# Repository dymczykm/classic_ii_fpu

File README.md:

# Macintosh Classic II FPU card

This repo contains a KiCAD design of an expansion card that adds an MC68882 FPU to your Macintosh Classic II. The board has two layers to keep the PCB cost down. It offers a switchable clock source between the system clock (16 MHz, synchronous operation) and a crystal oscillator on the board (40 MHz, asynchronous operation; tested with MC68882FN40A, the rumours claim 50 MHz will work too).

### Results

After plugging in the card, it should be immediately visible in some tools (here System Information of MacBench):

The board dramatically improves the Floating Point performance of the computer. MacBench 1.0 with an FPU@16 MHz (system clock) reports over a 13x improvement.
When using an external 40 MHz oscillator, the Floating Point result goes up even a bit more - to 15.7x (it's not proportional to the clock frequency as at some point the slow 16-bit bus becomes a limiting factor):

(look at the Floating Point row)

### Order a PCB

If you want to order a PCB directly, I have created a project on PCBWay:
https://www.pcbway.com/project/shareproject/Macintosh_Classic_II_FPU_card.html

### Bill of Materials

| Qty | Value           | Device             | Package              | Parts                                                  | Digikey reference             | 
|-----|-----------------|--------------------|----------------------|--------------------------------------------------------|-------------------------------|
| 1   |                 | MC68882FN40A       | PLCC68               | IC1                                                    |                               | 
| 1   |                 | PLCC68 socket      | PLCC68               | hosts IC1                                              | 2057-PLCC-68-AT-ND            | 
| 1   |                 | TE 5-532955-8      |                      | J2                                                     | A34313-ND                     | 
| 1   |                 | Pin Header 2.54mm  | 3 pins               | J1                                                     |                               |
| 6   | 100nF X7R       | SMD capacitor      | 0805                 | C1-C5, C7                                              | 399-17169-6-ND                | 
| 1   | 10uF 10V        | Tantalum Cap       | A (3216)             | C6                                                     | 399-4788-1-ND                 | 
| 1   | 51 ohm          | SMD resistor       | 0805                 | R1                                                     | A126374CT-ND                  | 
| 1   | 40 MHz          | Crystal oscillator | DIP-8                | X1                                                     | e.g. MXO45HS-2C-40M000000     | 
| 1   |                 | Shunt jumper       |                      | over J1                                                | 881545-1                      | 

(sorry, I had most components at hand, so I only have Digikey references for the rather specific ones)

### Pictures

### References and Credits

The MC68000 KiCAD library from https://dev.sigpipe.me/DashieElectronics/Jackalope

Thanks to [pfuentes69](https://github.com/pfuentes69) for providing the missing Digikey PNs.

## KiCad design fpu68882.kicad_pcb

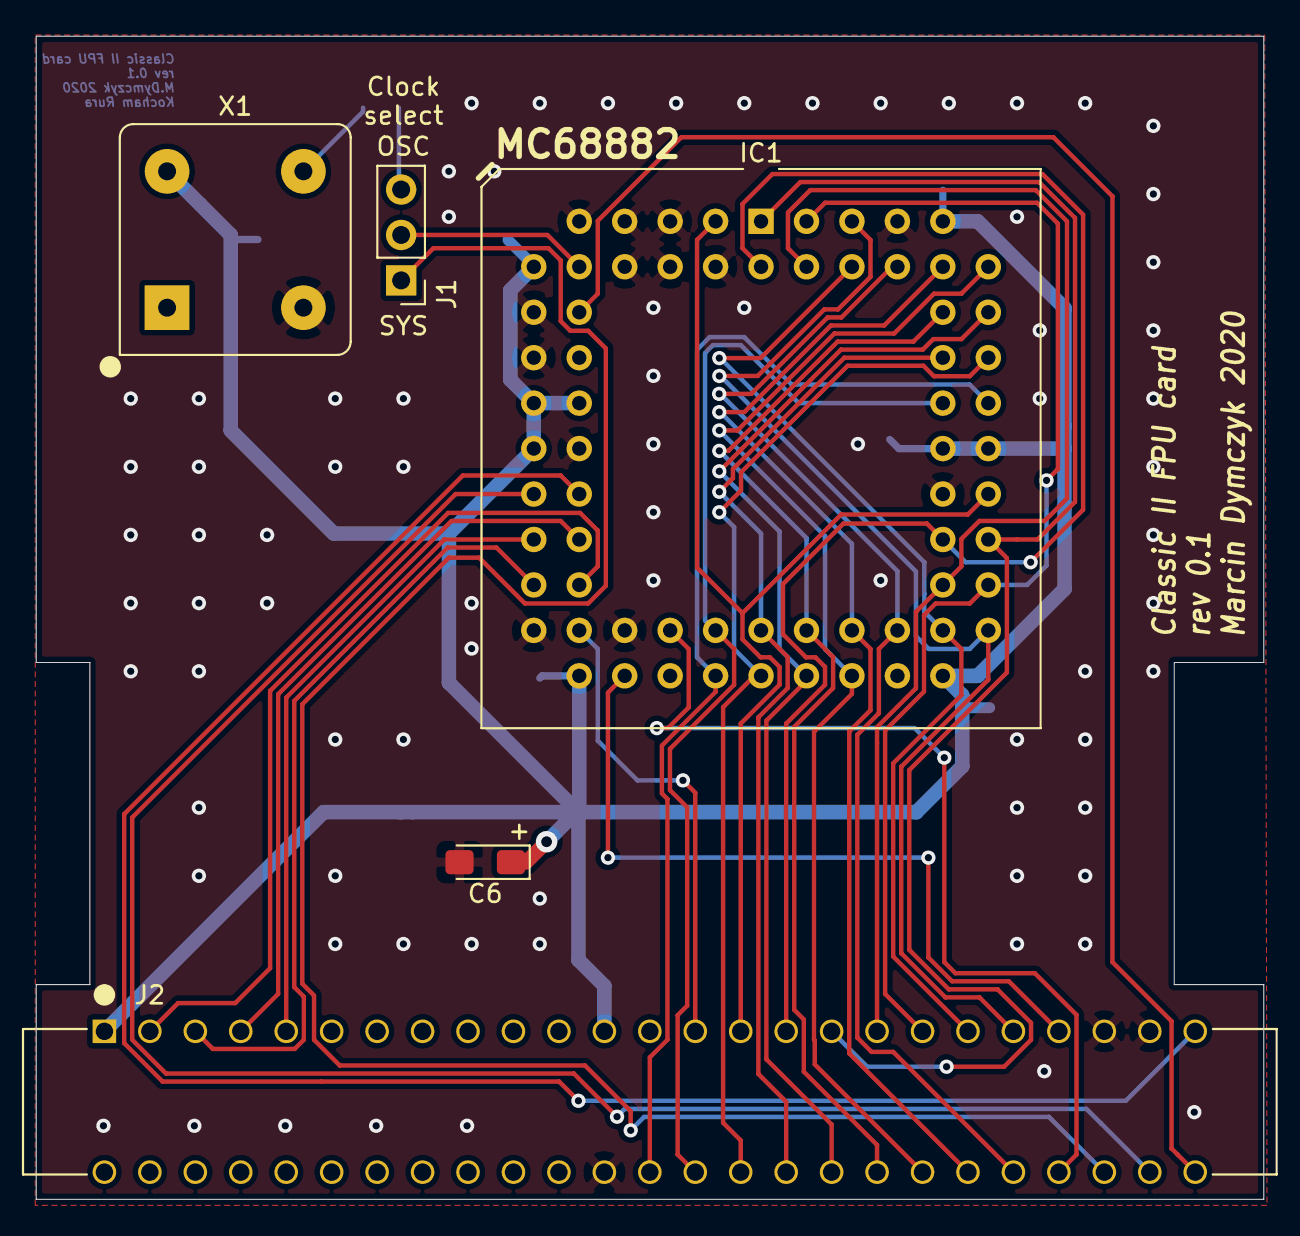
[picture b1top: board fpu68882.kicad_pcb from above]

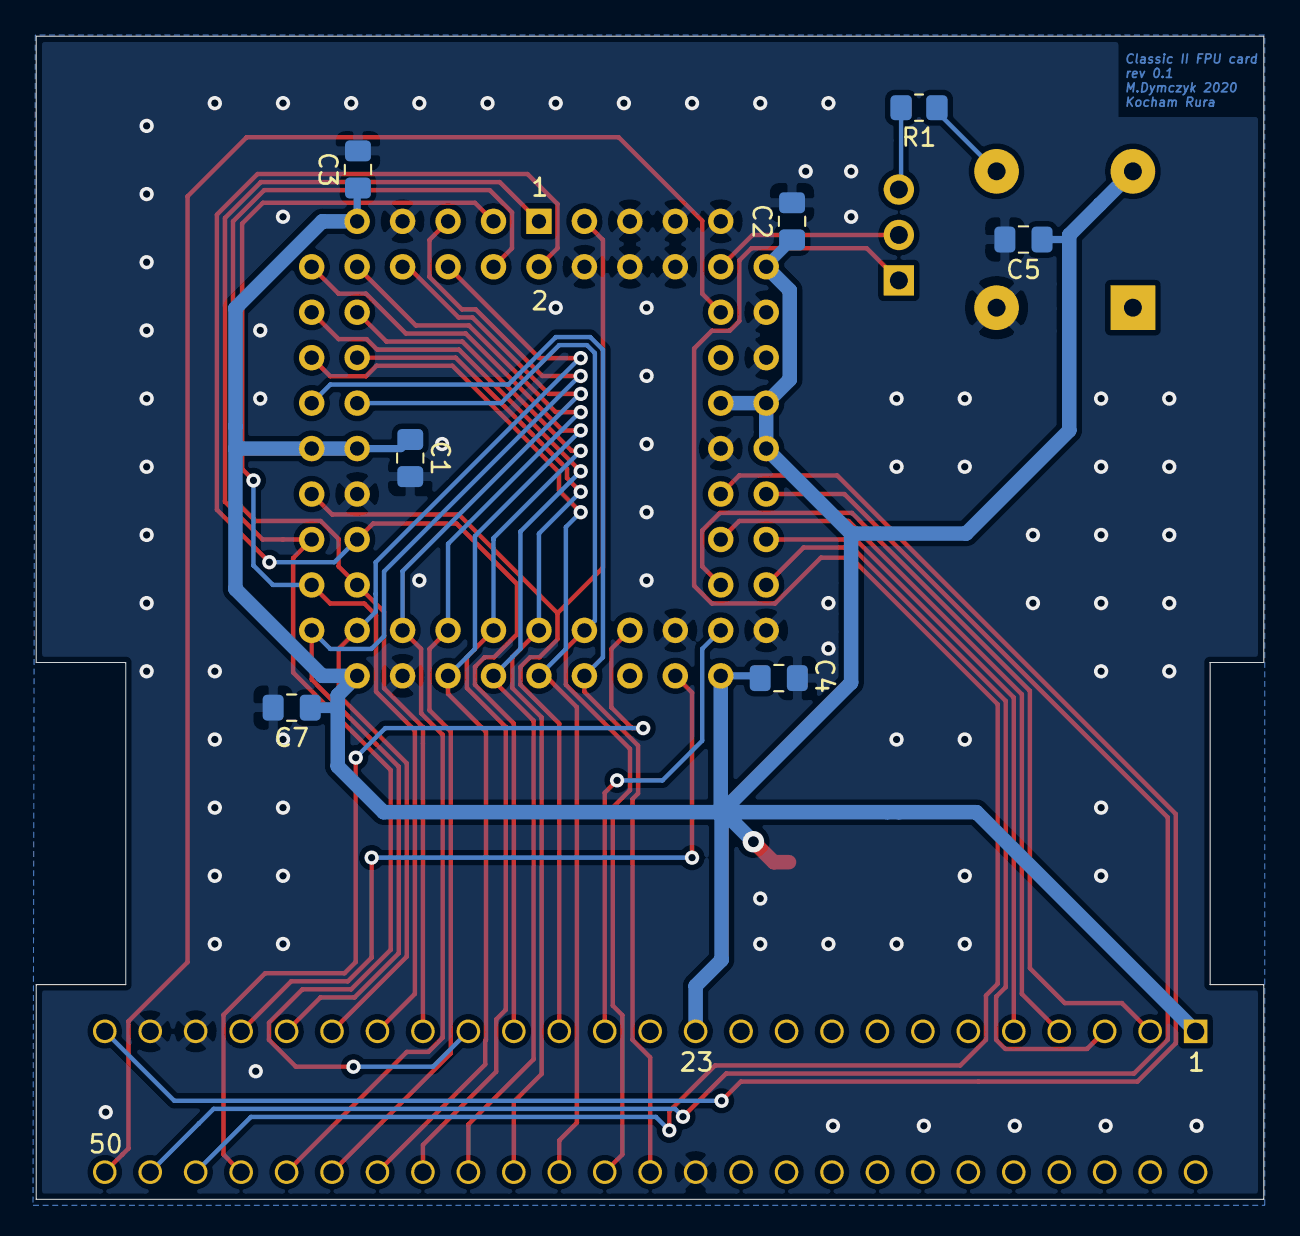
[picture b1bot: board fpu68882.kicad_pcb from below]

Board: 2 copper layers, 68.6 x 65.0 mm, 12 parts (7 on the bottom side), 32 nets.

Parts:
C1, C2, C3, C4, C5, C7: 100n; C_0805_2012Metric_Pad1.18x1.45mm_HandSolder
C6: 4u7; CP_EIA-3216-18_Kemet-A_Pad1.58x1.35mm_HandSolder
IC1: MC68881FN; PLCC-68_THT-Socket
J1: Conn_01x03; PinHeader_1x03_P2.54mm_Vertical
J2: Conn_02x25_Odd_Even; TE_5-532955-8_Odd_Even
R1: 33; R_0805_2012Metric_Pad1.20x1.40mm_HandSolder
X1: CXO_DIP8_40M; Oscillator_DIP-8_LargePads

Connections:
/A1: IC1.25, J2.3
/A2: IC1.24, J2.5
/A3: IC1.23, J2.7
/A4: IC1.22, J2.9
/C16M: J1.1, J2.46
/D16: IC1.3, IC1.50, J2.29
/D17: IC1.2, IC1.49, J2.31
/D18: IC1.1, IC1.48, J2.33
/D19: IC1.47, IC1.68, J2.35
/D20: IC1.46, IC1.67, J2.37
/D21: IC1.45, IC1.66, J2.39
/D22: IC1.44, IC1.65, J2.41
/D23: IC1.42, IC1.64, J2.42
/D24: IC1.40, IC1.62, J2.40
/D25: IC1.39, IC1.60, J2.38
/D26: IC1.38, IC1.59, J2.36
/D27: IC1.37, IC1.58, J2.34
/D28: IC1.36, IC1.57, J2.32
/D29: IC1.35, IC1.56, J2.30
/D30: IC1.34, IC1.55, J2.28
/D31: IC1.33, IC1.54, J2.26
/\AS: IC1.21, J2.49
/\DS: IC1.20, J2.48
/\DSACK1: IC1.32, J2.44
/\FPU.SEL: IC1.29, J2.43
/\RESET: IC1.13, J2.50
/\RW: IC1.28, J2.27
GND: C1.2, C2.2, C3.2, C4.2, C5.2, C6.2, C7.2, IC1.4, IC1.5, IC1.6, IC1.7, IC1.8, IC1.9, IC1.12, IC1.14, IC1.19, IC1.26, IC1.30, IC1.41, IC1.51, IC1.63, J2.24, J2.45, J2.47, X1.4
unnamed: IC1.11, J1.2
unnamed: J1.3, R1.2
unnamed: R1.1, X1.5
VDD: C1.1, C2.1, C3.1, C4.1, C5.1, C6.1, C7.1, IC1.10, IC1.16, IC1.17, IC1.18, IC1.27, IC1.43, IC1.52, IC1.53, IC1.61, J2.1, J2.23, X1.8

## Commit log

2020-12-28 First revision
2020-12-28 Added the DCM file
2020-12-28 Commit real files, fix the relative library path.
2020-12-28 Update the readme
2020-12-28 Add LICENSE
2020-12-28 add part number.
2021-01-27 Add a BOM and a better description to README, no images yet.
2021-01-27 Add images.
2021-01-27 Add pictures to README.md.
2021-01-28 Add a digikey PN for the oscillator.
2021-01-29 Added more Digikey PNs to README.md, thanks @pfuentes69.
2021-03-04 Added C7 to the BoM, thanks @pfuentes69.
2021-03-04 Correct J1/J2 naming in README.
